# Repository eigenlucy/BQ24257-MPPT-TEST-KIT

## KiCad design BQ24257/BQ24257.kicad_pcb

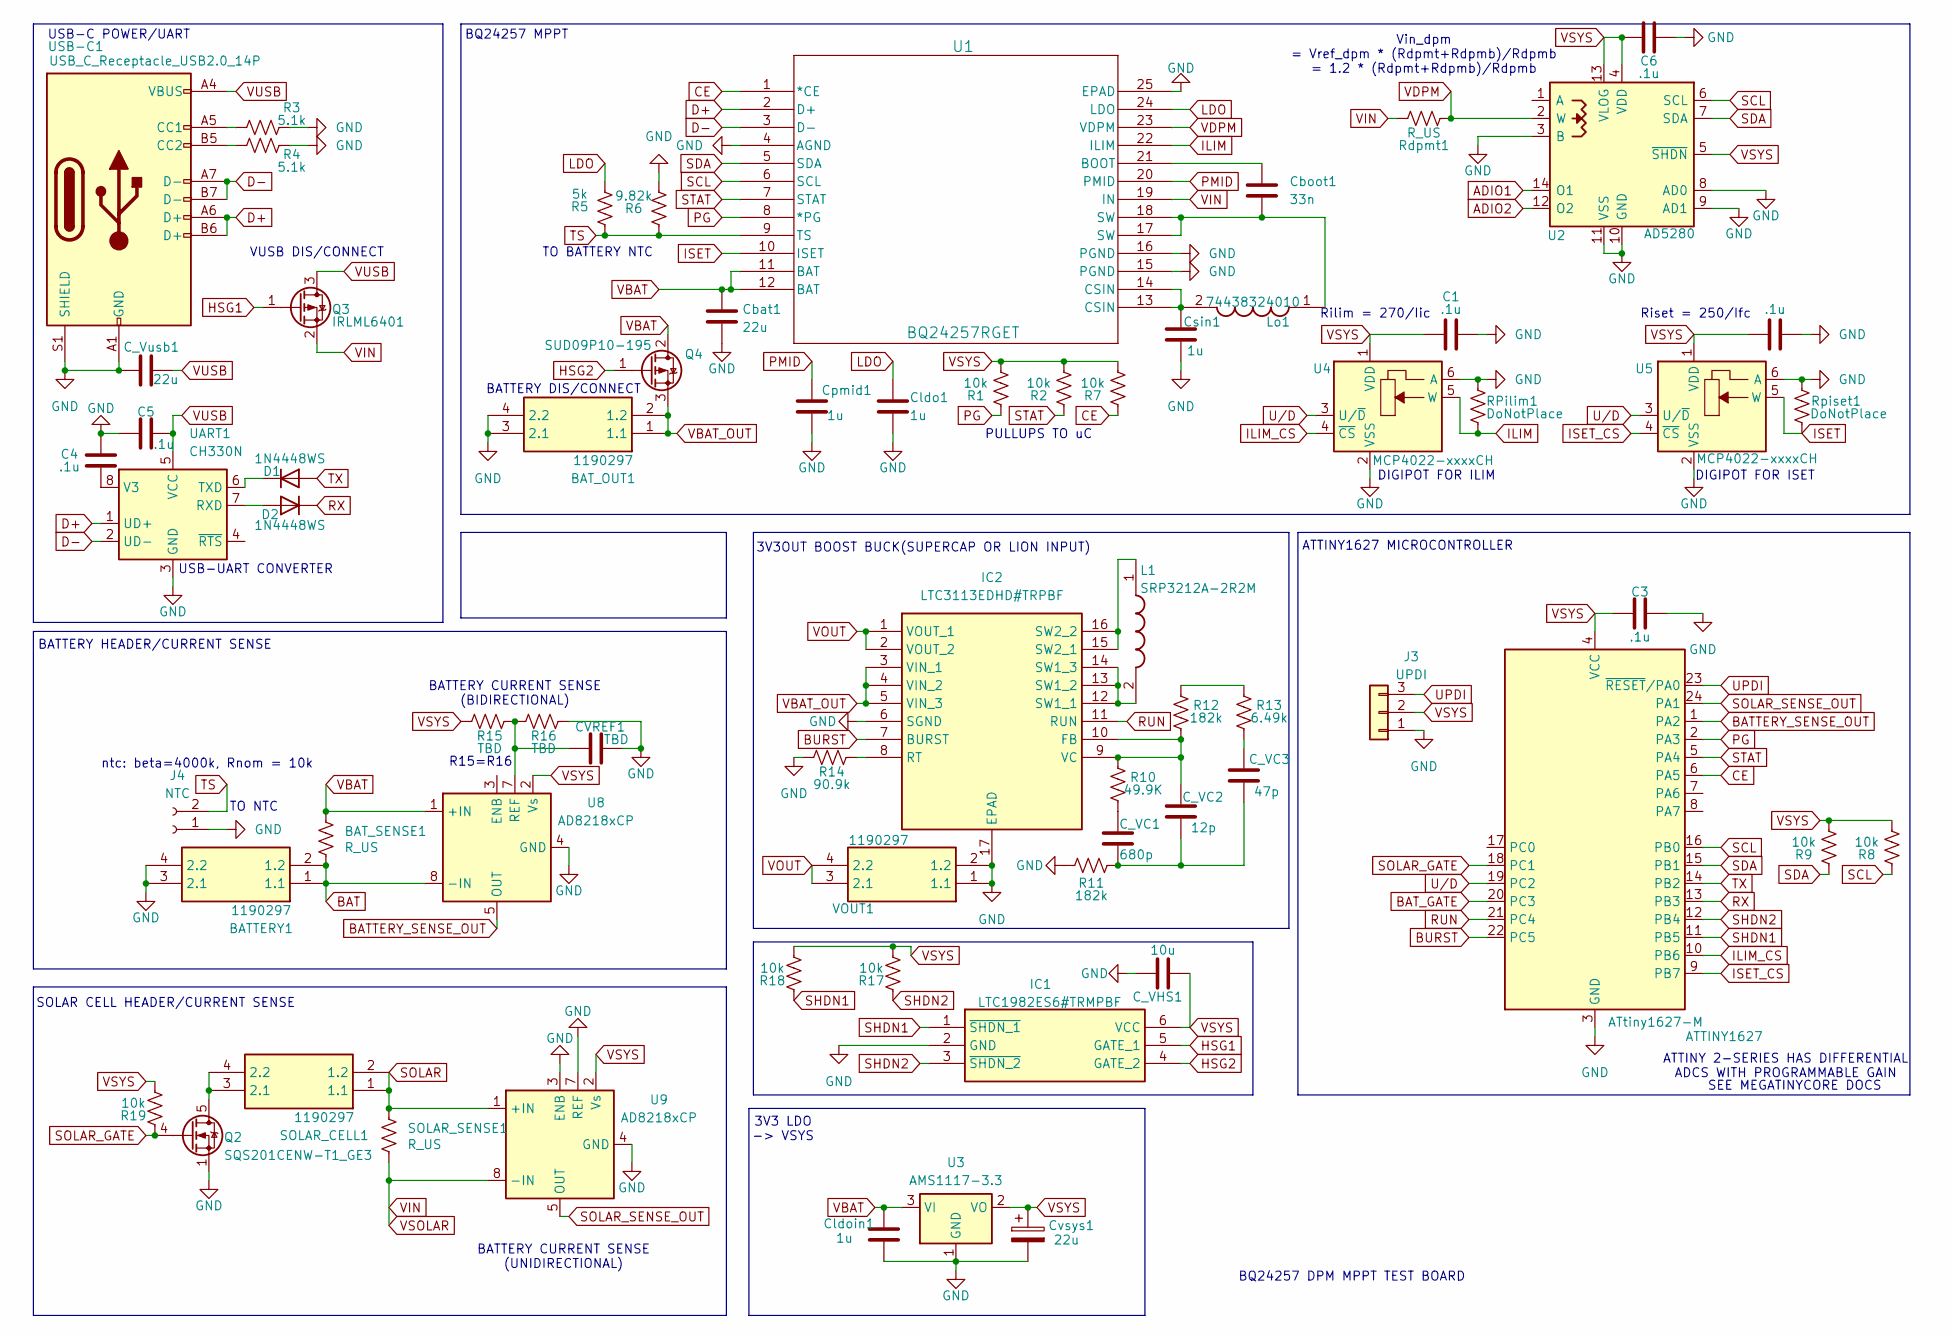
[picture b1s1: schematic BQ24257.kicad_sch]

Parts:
ATTINY1627: ATtiny1627-M; QFN-24-1EP_4x4mm_P0.5mm_EP2.6x2.6mm
BATTERY1: 1190297; Mouser Part Number 651-1190297
BAT_OUT1: 1190297; Mouser Part Number 651-1190297
BAT_SENSE1: R_US; R_1206_3216Metric
C1, C2, C3, C4, C5, C6: .1u; C_0402
CVREF1: TBD; C_0402
C_VC1: 680p; C_0402
C_VC2: 12p; C_0402
C_VC3: 47p; C_0402
C_VHS1: 10u; C_0603
C_Vusb1: 22u; C_0603
Cbat1: 22u; C_0603
Cboot1: 33n; C_0402
Cldo1: 1u; C_0402
Cldoin1: 1u; C_0402
Cpmid1: 1u; C_0402
Csin1: 1u; C_0402
Cvsys1: 22u; CP_Tantalum_EIA-6032-28_Kemet-C
D1, D2: 1N4448WS; D_SOD-323
IC1: LTC1982ES6#TRMPBF; SOT95P280X145-6N; Mouser Part Number 584-LTC1982ES6TRMPBF
IC2: LTC3113EDHD#TRPBF; SON50P400X500X80-17N-D; Mouser Part Number 584-LTC3113EDHDTRPBF
J3: UPDI; Pins_1x03_2.54mm_TH; Part Number 1-0301FBV0T
J4: NTC; Pins_1x02_2.54mm_TH
L1: SRP3212A-2R2M; INDC3225X120N; Mouser Part Number 652-SRP3212A-2R2M
Lo1: 74438324010; Mouser Part Number 710-74438324010
Q2: SQS201CENW-T1_GE3; PowerPAK_SO-8_Single
Q3: IRLML6401; SOT-23
Q4: SUD09P10-195; TO-252-2
R1, R2, R7, R8, R9, R17, R18, R19: 10k; R_0402
R3, R4: 5.1k; R_0402
R5: 5k; R_0402
R6: 9.82k; R_0402
R10: 49.9K; R_0402
R11, R12: 182k; R_0402
R13: 6.49k; R_0402
R14: 90.9k; R_0402
R15, R16: TBD; R_0402
RPilim1: DoNotPlace; R_0402
Rdpmt1: R_US; R_0402
Rpiset1: DoNotPlace; R_0402
SOLAR_CELL1: 1190297; Mouser Part Number 651-1190297
SOLAR_SENSE1: R_US; R_1206_3216Metric
U1: BQ24257RGET; RGE24_2P7X2P7_TEX
U2: AD5280; TSSOP-14_4.4x5mm_P0.65mm
U3: AMS1117-3.3; SOT223
U4, U5: MCP4022-xxxxCH; TSOT-23-6
U8, U9: AD8218xCP; SOP65P490X110-8N
UART1: CH330N; SOIC-8-1EP_3.9x4.9mm_Pitch1.27mm
USB-C1: USB_C_Receptacle_USB2.0_14P; USB_C_Receptacle_Palconn_UTC16-G
VOUT1: 1190297; Mouser Part Number 651-1190297

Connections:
ADIO1: U2.14 (O1)
ADIO2: U2.12 (O2)
BAT: BATTERY1.1 (1.1), BATTERY1.2 (1.2), BAT_SENSE1.2, U8.8 (-IN)
BATTERY_SENSE_OUT: ATTINY1627.1 (PA2), U8.5 (OUT)
BAT_GATE: ATTINY1627.20 (PC3)
BURST: ATTINY1627.22 (PC5), IC2.7 (BURST)
CE: ATTINY1627.6 (PA5), R7.1, U1.1 (*CE)
D+: U1.2 (D+), UART1.1 (UD+), USB-C1.A6 (D+), USB-C1.B6 (D+)
D-: U1.3 (D-), UART1.2 (UD-), USB-C1.A7 (D-), USB-C1.B7 (D-)
GND: ATTINY1627.3 (GND), ATTINY1627.25 (GND), BATTERY1.3 (2.1), BATTERY1.4 (2.2), BAT_OUT1.3 (2.1), BAT_OUT1.4 (2.2), C1.2, C2.2, C3.2, C4.2, C5.2, C6.2, CVREF1.1, C_VHS1.1, C_Vusb1.2, Cbat1.2, Cldo1.2, Cldoin1.2, Cpmid1.2, Csin1.2, Cvsys1.2, IC1.2 (GND), IC2.6 (SGND), IC2.17 (EPAD), J3.1, J4.1, Q2.1 (S), Q2.2 (S), Q2.3 (S), R3.2, R4.2, R6.2, R11.2, R14.1, R16.2, RPilim1.1, Rpiset1.1, U1.4 (AGND), U1.15 (PGND), U1.16 (PGND), U1.25 (EPAD), U1.V, U2.3 (B), U2.8 (AD0), U2.9 (AD1), U2.10 (GND), U2.11 (VSS), U3.1 (GND), U4.2 (VSS), U4.6 (A), U5.2 (VSS), U5.6 (A), U8.4 (GND), U8.9 (GND), U9.3 (ENB), U9.4 (GND), U9.7 (REF), U9.9 (GND), UART1.3 (GND), UART1.9, USB-C1.A1 (GND), USB-C1.A12 (GND), USB-C1.B1 (GND), USB-C1.B12 (GND), USB-C1.S1 (SHIELD), VOUT1.1 (1.1), VOUT1.2 (1.2)
HSG1: IC1.5 (GATE_1), Q3.1 (G)
HSG2: IC1.4 (GATE_2), Q4.1 (G)
ILIM: RPilim1.2, U1.22 (ILIM), U4.5 (W)
ILIM_CS: ATTINY1627.10 (PB6), U4.4 (~CS)
ISET: Rpiset1.2, U1.10 (ISET), U5.5 (W)
ISET_CS: ATTINY1627.9 (PB7), U5.4 (~CS)
LDO: Cldo1.1, R5.2, U1.24 (LDO)
unnamed: C_VC1.1, C_VC2.1, C_VC3.1, R11.1
unnamed: C_VC1.2, R10.2
unnamed: C_VC3.2, R13.2
unnamed: Cboot1.2, Lo1.1, U1.17 (SW), U1.18 (SW)
unnamed: Csin1.1, Lo1.2, U1.13 (CSIN), U1.14 (CSIN)
unnamed: D1.1 (K), UART1.6 (TXD)
unnamed: D2.2 (A), UART1.7 (RXD)
unnamed: C_VC2.2, IC2.9 (VC), IC2.10 (FB), R10.1, R12.2
unnamed: IC2.8 (RT), R14.2
unnamed: IC2.12 (SW1_1), IC2.13 (SW1_2), IC2.14 (SW1_3), L1.2
unnamed: IC2.15 (SW2_1), IC2.16 (SW2_2), L1.1
unnamed: Q2.5 (D), SOLAR_CELL1.3 (2.1), SOLAR_CELL1.4 (2.2)
unnamed: R12.1, R13.1
unnamed: Cboot1.1, U1.21 (BOOT)
unnamed: CVREF1.2, R15.2, R16.1, U8.7 (REF)
unnamed: C4.1, UART1.8 (V3)
unnamed: R3.1, USB-C1.A5 (CC1)
unnamed: R4.1, USB-C1.B5 (CC2)
PG: ATTINY1627.2 (PA3), R1.1, U1.8 (*PG)
PMID: Cpmid1.1, U1.20 (PMID)
RUN: ATTINY1627.21 (PC4), IC2.11 (RUN)
RX: ATTINY1627.13 (PB3), D2.1 (K)
SCL: ATTINY1627.16 (PB0), R8.1, U1.6 (SCL), U2.6 (SCL)
SDA: ATTINY1627.15 (PB1), R9.1, U1.5 (SDA), U2.7 (SDA)
SHDN1: ATTINY1627.11 (PB5), IC1.1 (~SHDN_1), R18.1
SHDN2: ATTINY1627.12 (PB4), IC1.3 (~SHDN_2), R17.1
SOLAR: SOLAR_CELL1.1 (1.1), SOLAR_CELL1.2 (1.2), SOLAR_SENSE1.1, U9.1 (+IN)
SOLAR_GATE: ATTINY1627.18 (PC1), Q2.4 (G), R19.1
SOLAR_SENSE_OUT: ATTINY1627.24 (PA1), U9.5 (OUT)
STAT: ATTINY1627.5 (PA4), R2.1, U1.7 (STAT)
TS: J4.2, R5.1, R6.1, U1.9 (TS)
TX: ATTINY1627.14 (PB2), D1.2 (A)
UPDI: ATTINY1627.23 (~RESET/PA0), J3.3
U/D: ATTINY1627.19 (PC2), U4.3 (U/~D), U5.3 (U/~D)
VBAT: BAT_SENSE1.1, Cbat1.1, Cldoin1.1, Q4.2 (D), U1.11 (BAT), U1.12 (BAT), U3.3 (VI), U8.1 (+IN)
VBAT_OUT: BAT_OUT1.1 (1.1), BAT_OUT1.2 (1.2), IC2.3 (VIN_1), IC2.4 (VIN_2), IC2.5 (VIN_3), Q4.3 (S)
VDPM: Rdpmt1.1, U1.23 (VDPM), U2.2 (W)
VIN: Q3.2 (S), Rdpmt1.2, SOLAR_SENSE1.2, U1.19 (IN), U9.8 (-IN)
VOUT: IC2.1 (VOUT_1), IC2.2 (VOUT_2), VOUT1.3 (2.1), VOUT1.4 (2.2)
VSYS: ATTINY1627.4 (VCC), C1.1, C2.1, C3.1, C6.1, C_VHS1.2, Cvsys1.1, IC1.6 (VCC), J3.2, R1.2, R2.2, R7.2, R8.2, R9.2, R15.1, R17.2, R18.2, R19.2, U2.4 (VDD), U2.5 (~SHDN), U2.13 (VLOG), U3.2 (VO), U4.1 (VDD), U5.1 (VDD), U8.2 (Vs), U9.2 (Vs)
VUSB: C5.1, C_Vusb1.1, Q3.3 (D), UART1.5 (VCC), USB-C1.A4 (VBUS), USB-C1.A9 (VBUS), USB-C1.B4 (VBUS), USB-C1.B9 (VBUS)

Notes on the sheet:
BATTERY CURRENT SENSE (BIDIRECTIONAL)
3V3 LDO -> VSYS
PULLUPS TO uC
TO BATTERY NTC
USB-UART CONVERTER
DIGIPOT FOR ILIM
BATTERY CURRENT SENSE (UNIDIRECTIONAL)
DIGIPOT FOR ISET
Riset = 250/Ifc
BQ24257 MPPT
BATTERY HEADER/CURRENT SENSE
SOLAR CELL HEADER/CURRENT SENSE
ntc: beta=4000k, Rnom = 10k
USB-C POWER/UART
ATTINY 2-SERIES HAS DIFFERENTIAL ADCS WITH PROGRAMMABLE GAIN
Rilim = 270/Iic
SEE MEGATINYCORE DOCS
R15=R16
VUSB DIS/CONNECT
3V3OUT BOOST BUCK(SUPERCAP OR LION INPUT)
ATTINY1627 MICROCONTROLLER
BQ24257 DPM MPPT TEST BOARD
TO NTC
Vin_dpm = Vref_dpm * (Rdpmt+Rdpmb)/Rdpmb = 1.2 * (Rdpmt+Rdpmb)/Rdpmb
BATTERY DIS/CONNECT

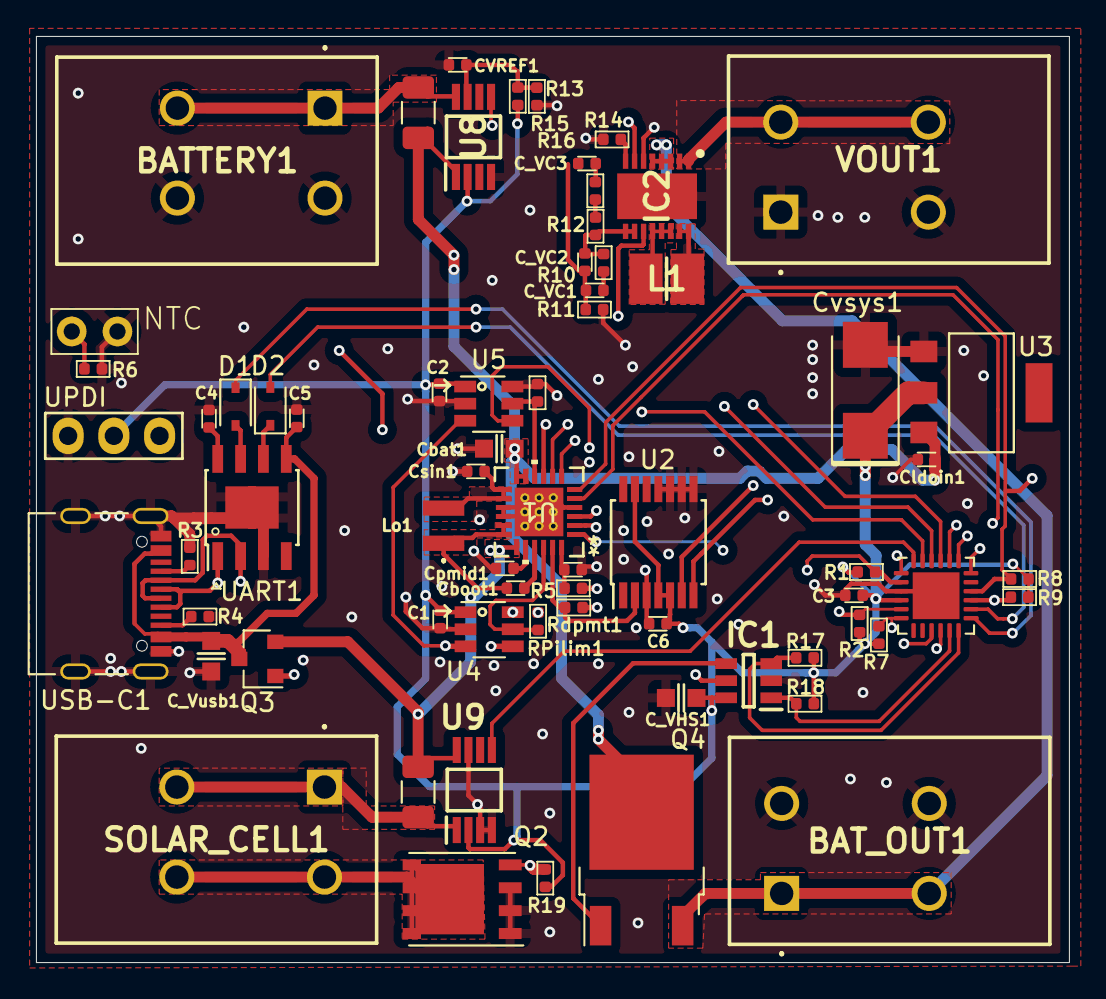
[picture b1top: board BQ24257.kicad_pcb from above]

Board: 4 copper layers, 57.4 x 51.4 mm, 68 parts (0 on the bottom side), 55 nets.

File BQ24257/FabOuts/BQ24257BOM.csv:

"Id";"Designator";"Footprint";"Quantity";"Designation";"Supplier and ref";
1;"R5";"R_0402";1;"5k";;;
2;"C_VHS1";"C_0603";1;"10u";;;
3;"R18,R17,R8,R9,R1,R2,R7,R19";"R_0402";8;"10k";;;
4;"C_VC2";"C_0402";1;"12p";;;
5;"SOLAR_SENSE1,BAT_SENSE1";"R_1206_3216Metric";2;"R_US";;;
6;"USB-C1";"USB_C_Receptacle_Palconn_UTC16-G";1;"USB_C_Receptacle_USB2.0_14P";;;
7;"J4";"Pins_1x02_2.54mm_TH";1;"NTC";;;
8;"J3";"Pins_1x03_2.54mm_TH";1;"UPDI";;;
9;"C2,C5,C4,C1,C3,C6";"C_0402";6;".1u";;;
10;"D2,D1";"D_SOD-323";2;"1N4448WS";;;
11;"Rpiset1,RPilim1";"R_0402";2;"DoNotPlace";;;
12;"R6";"R_0402";1;"9.82k";;;
13;"U1";"RGE24_2P7X2P7_TEX";1;"BQ24257RGET";;;
14;"C_VC3";"C_0402";1;"47p";;;
15;"C_VC1";"C_0402";1;"680p";;;
16;"R4,R3";"R_0402";2;"5.1k";;;
17;"Lo1";"74438324010";1;"74438324010";;;
18;"R12,R11";"R_0402";2;"182k";;;
19;"R10";"R_0402";1;"49.9K";;;
20;"IC2";"SON50P400X500X80-17N-D";1;"LTC3113EDHD#TRPBF";;;
21;"R14";"R_0402";1;"90.9k";;;
22;"Cldo1,Cldoin1,Csin1,Cpmid1";"C_0402";4;"1u";;;
23;"BATTERY1,BAT_OUT1,VOUT1,SOLAR_CELL1";"1190297";4;"1190297";;;
24;"UART1";"SOIC-8-1EP_3.9x4.9mm_Pitch1.27mm";1;"CH330N";;;
25;"Q4";"TO-252-2";1;"SUD09P10-195";;;
26;"U8,U9";"SOP65P490X110-8N";2;"AD8218xCP";;;
27;"R16,R15";"R_0402";2;"TBD";;;
28;"L1";"INDC3225X120N";1;"SRP3212A-2R2M";;;
29;"Q2";"PowerPAK_SO-8_Single";1;"SQS201CENW-T1_GE3";;;
30;"Rdpmt1";"R_0402";1;"R_US";;;
31;"IC1";"SOT95P280X145-6N";1;"LTC1982ES6#TRMPBF";;;
32;"Cboot1";"C_0402";1;"33n";;;
33;"C_Vusb1,Cbat1";"C_0603";2;"22u";;;
34;"U4,U5";"TSOT-23-6";2;"MCP4022-xxxxCH";;;
35;"U3";"SOT223";1;"AMS1117-3.3";;;
36;"Cvsys1";"CP_Tantalum_EIA-6032-28_Kemet-C";1;"22u";;;
37;"Q3";"SOT-23";1;"IRLML6401";;;
38;"CVREF1";"C_0402";1;"TBD";;;
39;"U2";"TSSOP-14_4.4x5mm_P0.65mm";1;"AD5280";;;
40;"R13";"R_0402";1;"6.49k";;;
41;"ATTINY1627";"QFN-24-1EP_4x4mm_P0.5mm_EP2.6x2.6mm";1;"ATtiny1627-M";;;

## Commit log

2024-11-08 passed DRC
2024-11-11 submitted
